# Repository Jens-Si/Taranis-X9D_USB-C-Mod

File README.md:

# Taranis-X9D_USB-C-Mod

I was always looking for a microUSB cable. Therefore, I have developed a small circuit board to equip my Taranis X9D with a USB-C socket.

## Instalation
- Open the radio and take out the middle PCB with the USB connector.
- Desolder and replace the USB-PCB with the new one.
- Take a small file and widen the hole for the USB connector.

<p align="center">
  
  <br /> Old and new PCB
</p>

<p align="center">

  <br /> Installation of the new PCB
</p>
<p align="center">
  
  <br /> the "new" back of the radio :D
</p>

## PCB
In the folder "PCB" you can see the EAGLE project, if you want to have a look at it. <br />
Or you can upload the .zip file at places like JLCPCB and order the PCB straight away.

## BOM
You only need three components. The USB-C plug and 2x 5.1kOhm 0805 SMD Resistor. <br />
The folder "BOM" contains the datasheet for the USB-C plug, if you have to source a different one...

- 1x https://lcsc.com/product-detail/USB-Connectors_SOFNG-MC-311D_C136423.html
- 2x https://lcsc.com/product-detail/Chip-Resistor-Surface-Mount_UNI-ROYAL-Uniroyal-Elec-0805W8J0512T5E_C26023.html

## ...
i still have a few PCB's left... ;)

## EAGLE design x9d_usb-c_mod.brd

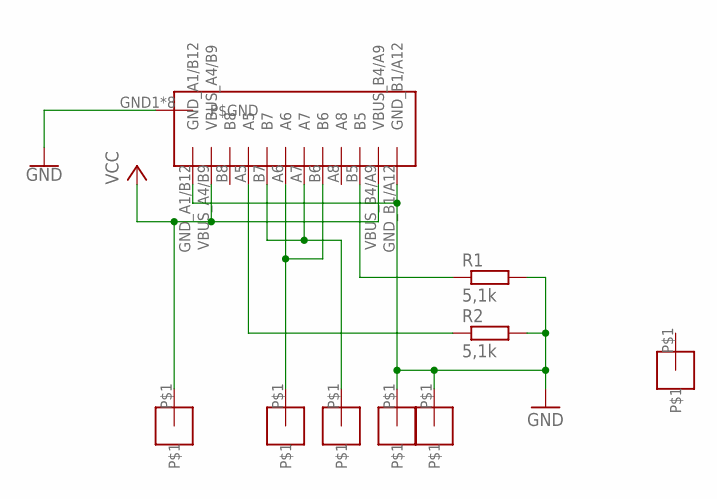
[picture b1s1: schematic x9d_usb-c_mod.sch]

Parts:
GND1: MOTORPADPAD_1X2; PAD_1X2
MID1, MID2, MID3, MID4, MID6: MOTORPADPAD_1X2; PAD_1X2
R1, R2: 5,1k; R0805
U$1: USB-C_2.0SOFNG_MC-331D; USB-C_MC-331D

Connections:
GND: GND1.P$1, MID1.P$1, R1.2, R2.2, U$1.GND1 (P$GND), U$1.GND2 (P$GND), U$1.GND3 (P$GND), U$1.GND4 (P$GND), U$1.GND5 (P$GND), U$1.GND6 (P$GND), U$1.GND7 (P$GND), U$1.GND8 (P$GND), U$1.GND_A1/B12, U$1.GND_B1/A12
unnamed: MID6.P$1, U$1.A7, U$1.B7
unnamed: MID3.P$1, U$1.A6, U$1.B6
unnamed: R1.1, U$1.B5
unnamed: R2.1, U$1.A5
VCC: MID2.P$1, U$1.VBUS_A4/B9, U$1.VBUS_B4/A9

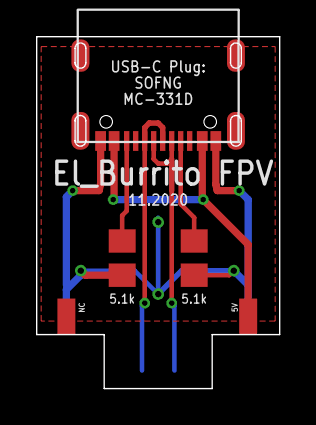
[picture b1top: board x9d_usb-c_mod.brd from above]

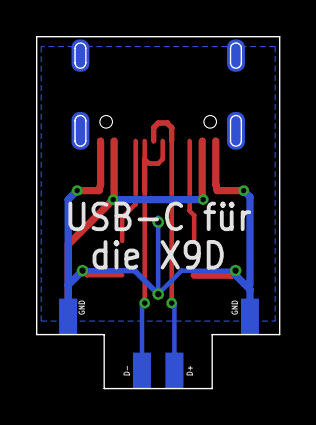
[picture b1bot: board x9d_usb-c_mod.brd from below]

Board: 2 copper layers, 13.5 x 19.6 mm, 9 parts (4 on the bottom side), 6 nets.

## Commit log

2022-04-07 Create PCB-Files
2022-04-07 Create test

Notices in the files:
parts and their libraries:
SparkFun-PowerSymbols: Licensing: Creative Commons ShareAlike 4.0 International - https://creativecommons.org/licenses/by-sa/4.0
